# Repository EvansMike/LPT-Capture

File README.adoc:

= LPT Capture

Capture text from a parallel port to a file, then convert that to a LibreOffice document. Assumes that the format is plain text.

This was written to capture the parallel print output from a Megger used for PAT.  It will likely work for other legacy devices with parallel LPT ports.

This consists of hardware/firmware in /firmware and PC, Linux, software in /userware.

Micro controller code is C AVR not Arduino.  To make the firmware:

[source, bash]
cd firmware
make install

To build and install.  Edit the Makefile for your favourite installer tool.

First build your device using the schematic.

I used perf-board and wires since the wiring is very simple.  Resistor values are 1K but other values around this may work too.
No resistors at all will also work but may expose your parallel port to currents it can's handle.
There should probably be voltage spike protection too with suitable diodes and/or a buffer chip. 

Compile the pc side utility with:

[source, bash]
cd userware
make install

== How to Use

- Plug it in to the port you want to capture from and a USB cable.
- Press Print on the device, a Megger AV4 in my case.  It should wait until a printer becomes attached
- Do:

[source, bash]
lpt_capture /dev/ttyUSB0 report.fodt

Command line arguments are input port and output file name.

Then don't open the output file.

Or rather use the LPT.log file as the  printfile.fodt wil be empty because this doesn't work
and I can't remember why anymore.

////[source, bash]
////libreoffice printfile.fodt

To open the file in LibreOffice Writer.
Or you can do all that mouse clicky malarky in your GUI.

Enjoy.  Also post bugs and improvements.

This was really a one off for some specific data I need to liberate.
I need to make it more generic.

Maybe.

I guess this could realistically convert direct to PDF but using LibreOffice to check and edit the output
is a useful intermediate step.  LibreOffice can do the conversion directly with:

[source, bash]
libreoffice7.0 --headless --convert-to pdf printfile.fodt

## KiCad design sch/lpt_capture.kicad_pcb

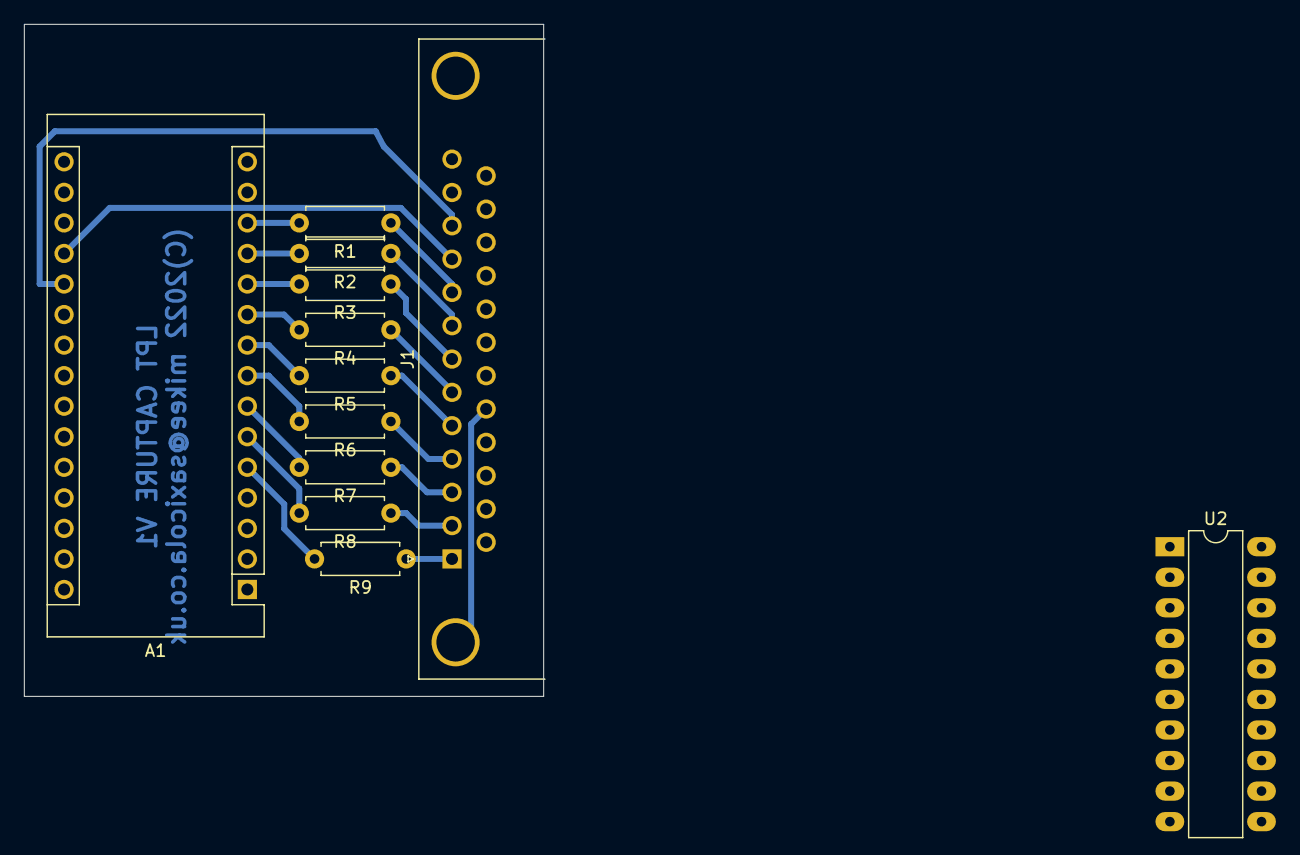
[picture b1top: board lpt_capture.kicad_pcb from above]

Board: 2 copper layers, 43.2 x 55.9 mm, 12 parts (0 on the bottom side), 21 nets.

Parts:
A1: Arduino_Nano_Every; Arduino_Nano
J1: DB25_Male_MountingHoles; DSUB-25_Male_Horizontal_P2.77x2.84mm_EdgePinOffset4.94mm_Ho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
R1, R2, R3, R4, R5, R6, R7, R8, R9: 1K; R_Axial_DIN0207_L6.3mm_D2.5mm_P7.62mm_Horizontal
U2: 74LS541; DIP-20_W7.62mm_LongPads

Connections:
/PB0: A1.11, R3.2
/PB1: A1.12, R2.2
/PB2: A1.13, R1.2
/PC0: A1.19, J1.10
/PC1: A1.20, J1.11
/PD2(INT0): A1.5, R9.2
/PD3: A1.6, R8.2
/PD4: A1.7, R7.2
/PD5: A1.8, R6.2
/PD6: A1.9, R5.2
/PD7: A1.10, R4.2
GND: A1.4, A1.29, J1.0, J1.12, J1.18, J1.19, J1.20, J1.21, J1.22, J1.23, J1.24, J1.25
unnamed: J1.1, R9.1
unnamed: J1.2, R8.1
unnamed: J1.3, R7.1
unnamed: J1.4, R6.1
unnamed: J1.5, R5.1
unnamed: J1.6, R4.1
unnamed: J1.7, R3.1
unnamed: J1.8, R2.1
unnamed: J1.9, R1.1

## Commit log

2020-12-23 More added files.
2020-12-23 modified: Makefile modified: main.c
2020-12-23 new file: main.h
2020-12-23 Add IO pin control
2020-12-23 Balls. Run out of pins. Need to use a ATmega...
2020-12-23 Convert to nano/mega168.
2020-12-24 New PCB files.
2020-12-24 Print test good.
2020-12-26 Works with an empty data file.
2020-12-26 Dealing with double quotes helped. Still not right though.
2020-12-26 More special chars delaing with.
2020-12-27 Add 1K resistors and a note to schematic.
2020-12-27 Add REAL port names to schematic.
2020-12-27 Change baud rate.
2020-12-27 new file: ../README.adoc
2020-12-27 Added more.
2020-12-27 Add schematic pdf. new file: ../sch/schematic.pdf
2020-12-27 Typos and edits.
2020-12-28 Read test working.
2020-12-28 This works.
    Need to fixup various file names and make it flixible.
2020-12-28 modified: ../README.adoc
2020-12-28 modified: ../README.adoc modified: eps_convert.c
2020-12-28 modified: eps_convert.c
2020-12-29 Add the simplest Makefile ever written.
2020-12-29 Clean up and and better debug statements.
2022-01-17 Minor edits.
2022-05-24 Typos.
2022-05-24 Rename dirs to something more meaningful.
2022-05-24 Small updates relating to dir renaming.
2022-05-24 Do the PCB.
2022-05-24 Notes edit.
2022-07-05 Fix pointer ‘fid’ used after ‘fclose’ [-Wuse-after-free]
2022-07-06 Extend timeout for slow printer.
2022-07-06 Shorten delay in ACK.
2022-07-06 Change output file name and update README.

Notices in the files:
sch/lpt_capture.kicad_pcb:
(C)2022 mikee@saxicola.co.uk
